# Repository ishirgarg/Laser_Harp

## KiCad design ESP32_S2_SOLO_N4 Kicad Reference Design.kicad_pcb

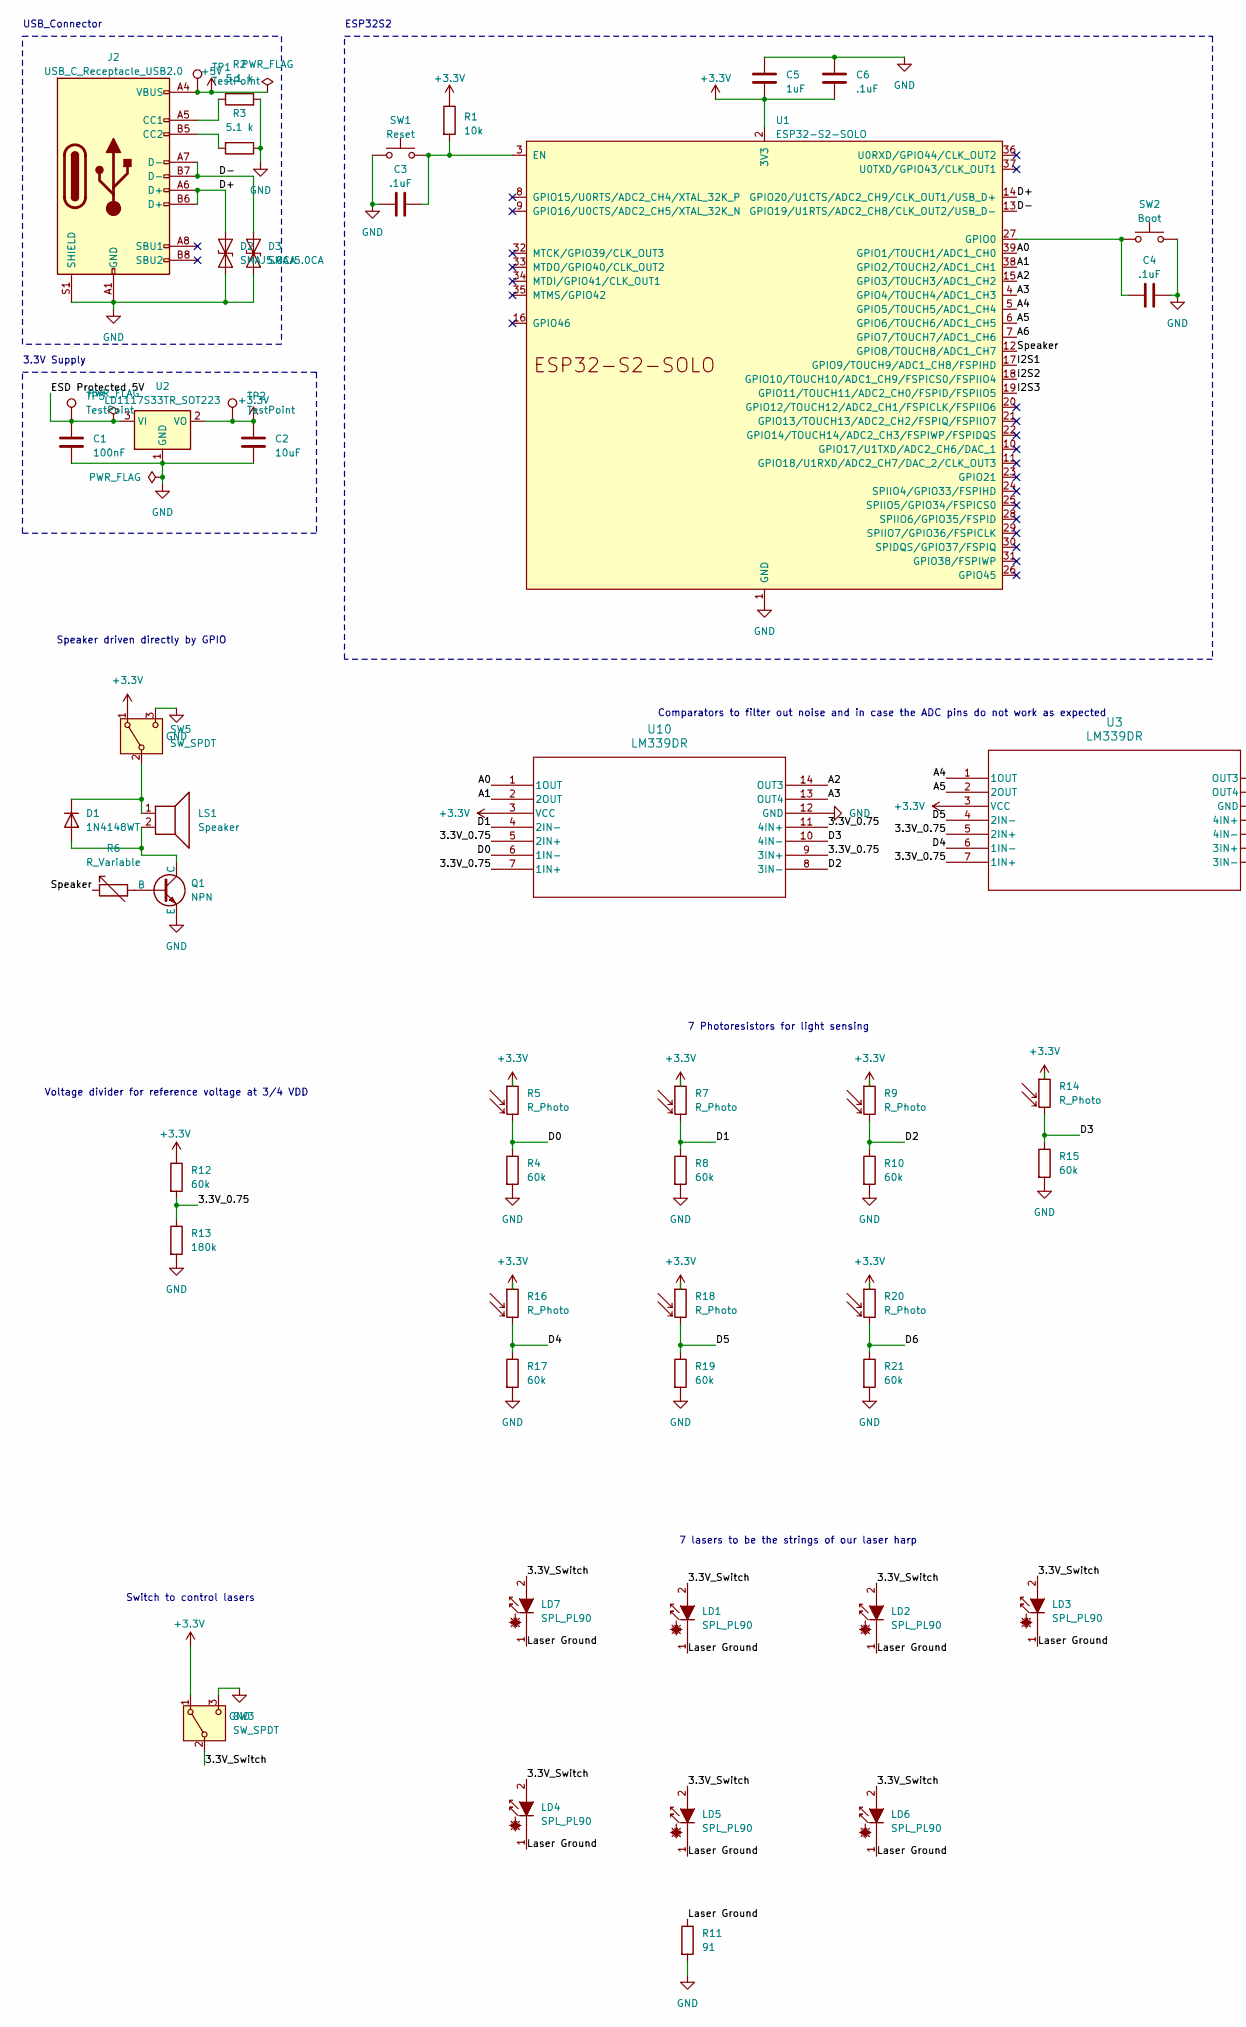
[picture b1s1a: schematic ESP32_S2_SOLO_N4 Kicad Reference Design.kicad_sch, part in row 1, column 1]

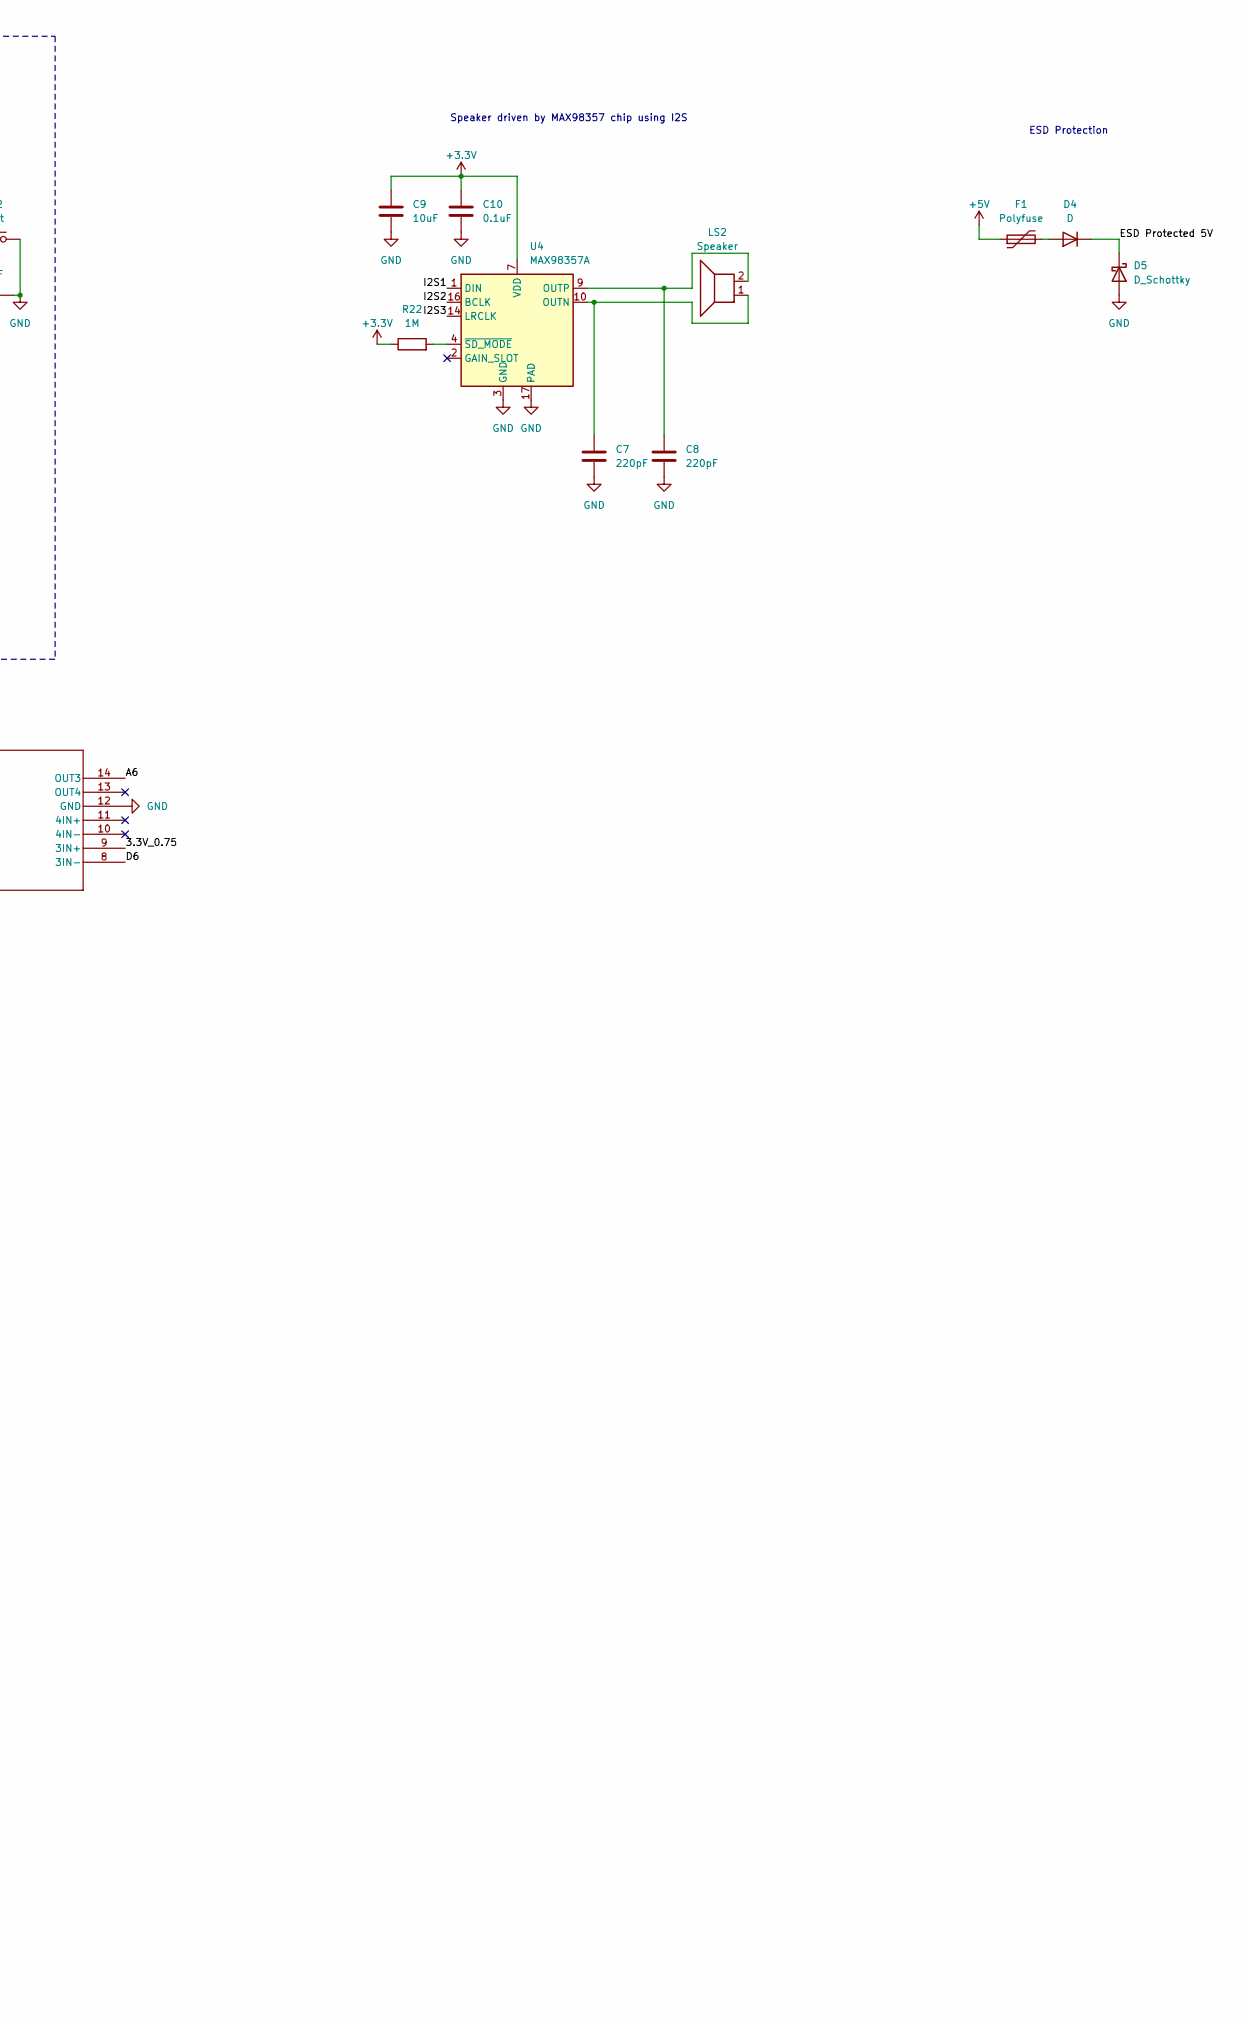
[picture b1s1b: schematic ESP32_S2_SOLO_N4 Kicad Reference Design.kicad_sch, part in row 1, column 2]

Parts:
C1: 100nF; C_0805_2012Metric_Pad1.18x1.45mm_HandSolder
C2, C9: 10uF; C_0805_2012Metric_Pad1.18x1.45mm_HandSolder
C3, C4, C6: .1uF; C_0805_2012Metric_Pad1.18x1.45mm_HandSolder
C5: 1uF; C_0805_2012Metric_Pad1.18x1.45mm_HandSolder
C7, C8: 220pF; C_0805_2012Metric_Pad1.18x1.45mm_HandSolder
C10: 0.1uF; C_0805_2012Metric_Pad1.18x1.45mm_HandSolder
D1: 1N4148WT; D_0805_2012Metric_Pad1.15x1.40mm_HandSolder
D2, D3: SMAJ5.0CA; D_SOD-323_HandSoldering
D4: D; D_0805_2012Metric_Pad1.15x1.40mm_HandSolder
D5: D_Schottky; D_0805_2012Metric_Pad1.15x1.40mm_HandSolder
F1: Polyfuse; D_0805_2012Metric_Pad1.15x1.40mm_HandSolder
J2: USB_C_Receptacle_USB2.0; USB_C_Receptacle_GCT_USB4105-xx-A_16P_TopMnt_Horizontal
LD1, LD2, LD3, LD4, LD5, LD6, LD7: SPL_PL90; PinSocket_1x02_P2.54mm_Vertical
LS1, LS2: Speaker; PinSocket_1x02_P2.54mm_Vertical
Q1: NPN; TSOT-23_HandSoldering
R1: 10k; R_0805_2012Metric_Pad1.20x1.40mm_HandSolder
R2, R3: 5.1 k; R_0805_2012Metric_Pad1.20x1.40mm_HandSolder
R4, R10, R12, R15, R17, R19, R21: 60k; R_0805_2012Metric_Pad1.20x1.40mm_HandSolder
R5, R7, R9, R14, R16, R18, R20: R_Photo; PinSocket_1x02_P2.54mm_Vertical
R6: R_Variable; R_Axial_DIN0207_L6.3mm_D2.5mm_P15.24mm_Horizontal
R8: 60k; R_0805_2012Metric
R11: 91; R_0805_2012Metric_Pad1.20x1.40mm_HandSolder
R13: 180k; R_0805_2012Metric_Pad1.20x1.40mm_HandSolder
R22: 1M; R_0805_2012Metric_Pad1.20x1.40mm_HandSolder
SW1: Reset; SWDIP2_256X170P100
SW2: Boot; SWDIP2_256X170P100
SW3, SW5: SW_SPDT; SW_DPDT_CK_JS202011JCQN
TP1, TP2, TP3: TestPoint; TestPoint_Plated_Hole_D2.0mm
U1: ESP32-S2-SOLO; XCVR_ESP32-S2-SOLO-N4
U2: LD1117S33TR_SOT223; SOT-223-3_TabPin2
U3, U10: LM339DR; D14
U4: MAX98357A; TQFN-16-1EP_3x3mm_P0.5mm_EP1.23x1.23mm

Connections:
+3.3V: C2.1, C5.2, C6.2, C9.1, C10.1, R1.1, R5.1, R7.1, R9.1, R12.1, R14.1, R16.1, R18.1, R20.1, R22.1, SW3.1 (A), SW5.1 (A), TP2.1, U1.2 (3V3), U2.2 (VO), U3.3 (VCC), U4.7 (VDD), U4.8 (VDD), U10.3 (VCC)
+5V: F1.1, J2.A4 (VBUS), J2.A9 (VBUS), J2.B4 (VBUS), J2.B9 (VBUS), TP1.1
/3.3V_0.75: R12.2, R13.1, U3.5 (2IN+), U3.7 (1IN+), U3.9 (3IN+), U10.5 (2IN+), U10.7 (1IN+), U10.9 (3IN+), U10.11 (4IN+)
/3.3V_Switch: LD1.2 (A), LD2.2 (A), LD3.2 (A), LD4.2 (A), LD5.2 (A), LD6.2 (A), LD7.2 (A), SW3.2 (B)
/A0: U1.39 (GPIO1/TOUCH1/ADC1_CH0), U10.1 (1OUT)
/A1: U1.38 (GPIO2/TOUCH2/ADC1_CH1), U10.2 (2OUT)
/A2: U1.15 (GPIO3/TOUCH3/ADC1_CH2), U10.14 (OUT3)
/A3: U1.4 (GPIO4/TOUCH4/ADC1_CH3), U10.13 (OUT4)
/A4: U1.5 (GPIO5/TOUCH5/ADC1_CH4), U3.1 (1OUT)
/A5: U1.6 (GPIO6/TOUCH6/ADC1_CH5), U3.2 (2OUT)
/A6: U1.7 (GPIO7/TOUCH7/ADC1_CH6), U3.14 (OUT3)
/D0: R4.1, R5.2, U10.6 (1IN-)
/D1: R7.2, R8.1, U10.4 (2IN-)
/D2: R9.2, R10.1, U10.8 (3IN-)
/D3: R14.2, R15.1, U10.10 (4IN-)
/D4: R16.2, R17.1, U3.6 (1IN-)
/D5: R18.2, R19.1, U3.4 (2IN-)
/D6: R20.2, R21.1, U3.8 (3IN-)
/D+: D2.2 (A2), J2.A6 (D+), J2.B6 (D+), U1.14 (GPIO20/U1CTS/ADC2_CH9/CLK_OUT1/USB_D+)
/D-: D3.2 (A2), J2.A7 (D-), J2.B7 (D-), U1.13 (GPIO19/U1RTS/ADC2_CH8/CLK_OUT2/USB_D-)
/ESD Protected 5V: C1.1, D4.1 (K), D5.1 (K), TP3.1, U2.3 (VI)
/I2S1: U1.17 (GPIO9/TOUCH9/ADC1_CH8/FSPIHD), U4.1 (DIN)
/I2S2: U1.18 (GPIO10/TOUCH10/ADC1_CH9/FSPICS0/FSPIIO4), U4.16 (BCLK)
/I2S3: U1.19 (GPIO11/TOUCH11/ADC2_CH0/FSPID/FSPIIO5), U4.14 (LRCLK)
/Laser Ground: LD1.1 (C), LD2.1 (C), LD3.1 (C), LD4.1 (C), LD5.1 (C), LD6.1 (C), LD7.1 (C), R11.1
/Speaker: R6.1, U1.12 (GPIO8/TOUCH8/ADC1_CH7)
GND: C1.2, C2.2, C3.1, C4.2, C5.1, C6.1, C7.2, C8.2, C9.2, C10.2, D2.1 (A1), D3.1 (A1), D5.2 (A), J2.A1 (GND), J2.A12 (GND), J2.B1 (GND), J2.B12 (GND), J2.S1 (SHIELD), Q1.3 (E), R2.2, R3.1, R4.2, R8.2, R10.2, R11.2, R13.2, R15.2, R17.2, R19.2, R21.2, SW1.1, SW2.2, SW3.3 (C), SW5.3 (C), U1.1 (GND), U1.40 (GND), U1.41 (GND), U2.1 (GND), U3.12 (GND), U4.3 (GND), U4.11 (GND), U4.15 (GND), U4.17 (PAD), U10.12 (GND)
unnamed: D1.2 (A), LS1.2, Q1.1 (C)
unnamed: D1.1 (K), LS1.1, SW5.2 (B)
unnamed: D4.2 (A), F1.2
unnamed: J2.A5 (CC1), R2.1
unnamed: J2.B5 (CC2), R3.2
unnamed: Q1.2 (B), R6.2
unnamed: C3.2, R1.2, SW1.2, U1.3 (EN)
unnamed: C4.1, SW2.1, U1.27 (GPIO0)
unnamed: C7.1, LS2.1, U4.10 (OUTN)
unnamed: C8.1, LS2.2, U4.9 (OUTP)
unnamed: R22.2, U4.4 (~SD_MODE)

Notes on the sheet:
7 lasers to be the strings of our laser harp
Speaker driven by MAX98357 chip using I2S
Voltage divider for reference voltage at 3/4 VDD
Comparators to filter out noise and in case the ADC pins do not work as expected
ESD Protection
7 Photoresistors for light sensing
Switch to control lasers
USB_Connector
ESP32S2
3.3V Supply
Speaker driven directly by GPIO

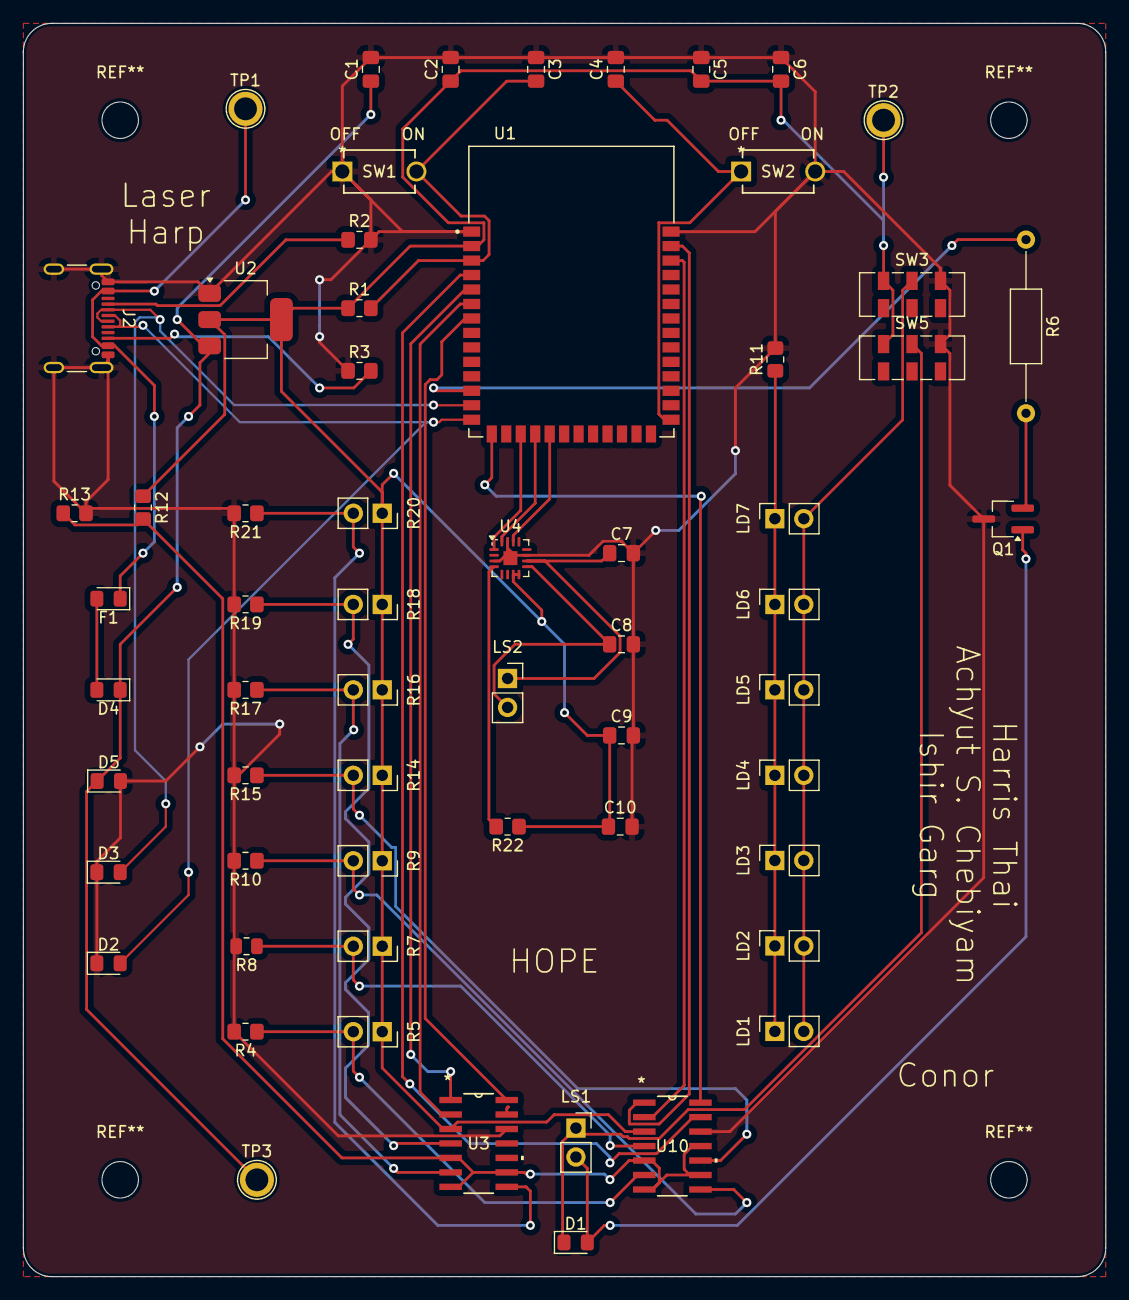
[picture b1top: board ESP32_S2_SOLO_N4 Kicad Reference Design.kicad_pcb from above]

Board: 2 copper layers, 95.0 x 110.0 mm, 61 parts (0 on the bottom side), 38 nets.

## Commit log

2024-04-11 finished schematic, footprints not done
2024-04-11 Footprints done
2024-04-12 Layout done
2024-04-12 I2S speaker and ESD protection schematic and footprints added
2024-04-12 Final project submission
